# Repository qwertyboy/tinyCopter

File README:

tinyCopter v2 - arduino based quadcopter project

Specifications:
	-Atmega328 @ 16MHz
	-ADXL345 Accelerometer and ITG-3200 Gyroscope
	-USB for debugging and updating
	-Reads standard R/C receiver
	-Uses the AeroQuad firmware

----OLD VERSION----

tinyCopter rev C - xmega based quadcopter project

Specifications:
	-xmega32a4u @ 32MHz
	-ADXL345 Accelerometer and ITG-3200 Gyroscope
	-USB for debugging and updating
	-Reads standard R/C receiver

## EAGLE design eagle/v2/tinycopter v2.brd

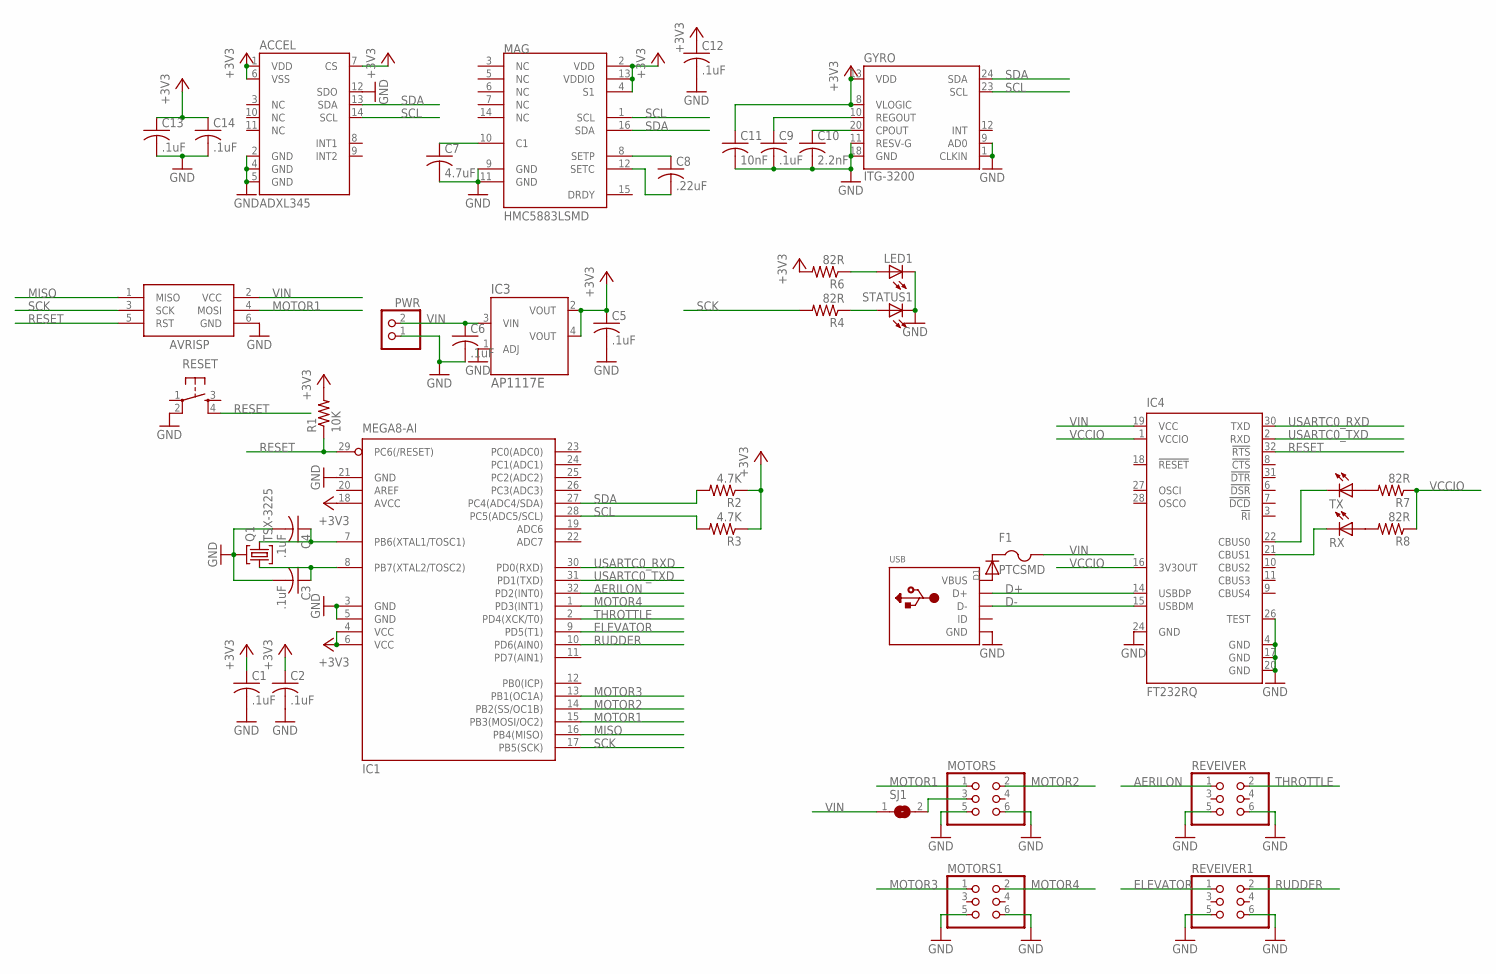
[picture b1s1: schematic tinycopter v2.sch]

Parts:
ACCEL: ADXL345; LGA14
AVRISP: AVRISP-6; AVRISP
C1, C2, C3, C4, C5, C6, C9, C12, C13, C14: .1uF; C0603
C7: 4.7uF; C0805K
C8: .22uF; C0603
C10: 2.2nF; C0603
C11: 10nF; C0603
D1: DIODESOD-123; SOD-123
F1: PTCSMD; 1812
GYRO: ITG-3200; QFN-24
IC1: MEGA8-AI; TQFP32-08
IC3: AP1117E; SOT223-3
IC4: FT232RQ; QFN32
LED1: LEDCHIP-LED0805; CHIP-LED0805
MAG: HMC5883LSMD; 16LPCC
MOTORS, MOTORS1: PINHD-2X3; 2X03
PWR: JST_2PIN-THM; JST-PH-2-THM
Q1: TSX-3225
R1: 10K; R0603
R2, R3: 4.7K; R0603
R4, R6, R7, R8: 82R; R0603
RESET: TAC_SWITCHSMD; TACTILE_SWITCH_SMD
REVEIVER, REVEIVER1: PINHD-2X3; 2X03
RX: LEDCHIP-LED0805; CHIP-LED0805
SJ1: SJ
STATUS1: LEDCHIP-LED0805; CHIP-LED0805
TX: LEDCHIP-LED0805; CHIP-LED0805
USB: USBMINIB; USB-MINIB

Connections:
+3V3: ACCEL.1 (VDD), ACCEL.6 (VSS), ACCEL.7 (CS), C1.1, C2.1, C5.1, C11.1, C12.1, C13.1, C14.1, GYRO.8 (VLOGIC), GYRO.13 (VDD), IC1.4 (VCC), IC1.6 (VCC), IC1.18 (AVCC), IC3.2 (VOUT), IC3.4 (VOUT), MAG.2 (VDD), MAG.4 (S1), MAG.13 (VDDIO), R1.2, R2.1, R3.1, R6.2
AERILON: IC1.32 (PD2(INT0)), REVEIVER.1
D+: IC4.14 (USBDP), USB.D+
D-: IC4.15 (USBDM), USB.D-
ELEVATOR: IC1.9 (PD5(T1)), REVEIVER1.1
GND: ACCEL.2 (GND), ACCEL.4 (GND), ACCEL.5 (GND), ACCEL.12 (SDO), AVRISP.6 (GND), C1.2, C2.2, C3.2, C4.2, C5.2, C6.2, C7.2, C9.2, C10.2, C11.2, C12.2, C13.2, C14.2, GYRO.1 (CLKIN), GYRO.9 (AD0), GYRO.11 (RESV-G), GYRO.18 (GND), IC1.3 (GND), IC1.5 (GND), IC1.21 (GND), IC3.1 (ADJ), IC4.4 (GND), IC4.17 (GND), IC4.20 (GND), IC4.24 (GND), IC4.26 (TEST), LED1.C, MAG.9 (GND), MAG.11 (GND), MOTORS.5, MOTORS.6, MOTORS1.5, MOTORS1.6, PWR.1 (2), Q1.2 (3), Q1.4 (3), RESET.2, REVEIVER.5, REVEIVER.6, REVEIVER1.5, REVEIVER1.6, STATUS1.C, USB.GND
MISO: AVRISP.1 (MISO), IC1.16 (PB4(MISO))
MOTOR1: AVRISP.4 (MOSI), IC1.15 (PB3(MOSI/OC2)), MOTORS.1
MOTOR2: IC1.14 (PB2(SS/OC1B)), MOTORS.2
MOTOR3: IC1.13 (PB1(OC1A)), MOTORS1.1
MOTOR4: IC1.1 (PD3(INT1)), MOTORS1.2
unnamed: C4.1, IC1.7 (PB6(XTAL1/TOSC1)), Q1.3 (2)
unnamed: C3.1, IC1.8 (PB7(XTAL2/TOSC2)), Q1.1
unnamed: R4.1, STATUS1.A
unnamed: C10.1, GYRO.20 (CPOUT)
unnamed: C7.1, MAG.10 (C1)
unnamed: C8.1, MAG.8 (SETP)
unnamed: LED1.A, R6.1
unnamed: C8.2, MAG.12 (SETC)
unnamed: C9.1, GYRO.10 (REGOUT)
unnamed: IC4.22 (CBUS0), TX.C
unnamed: IC4.21 (CBUS1), RX.C
unnamed: R7.2, TX.A
unnamed: D1.A, USB.VBUS
unnamed: R8.2, RX.A
unnamed: D1.C, F1.1
unnamed: MOTORS.3, SJ1.2
RESET: AVRISP.5 (RST), IC1.29 (PC6(/RESET)), IC4.32 (!RTS), R1.1, RESET.4
RUDDER: IC1.10 (PD6(AIN0)), REVEIVER1.2
SCK: AVRISP.3 (SCK), IC1.17 (PB5(SCK)), R4.2
SCL: ACCEL.14 (SCL), GYRO.23 (SCL), IC1.28 (PC5(ADC5/SCL)), MAG.1 (SCL), R3.2
SDA: ACCEL.13 (SDA), GYRO.24 (SDA), IC1.27 (PC4(ADC4/SDA)), MAG.16 (SDA), R2.2
THROTTLE: IC1.2 (PD4(XCK/T0)), REVEIVER.2
USARTC0_RXD: IC1.30 (PD0(RXD)), IC4.30 (TXD)
USARTC0_TXD: IC1.31 (PD1(TXD)), IC4.2 (RXD)
VCCIO: IC4.1 (VCCIO), IC4.16 (3V3OUT), R7.1, R8.1
VIN: AVRISP.2 (VCC), C6.1, F1.2, IC3.3 (VIN), IC4.19 (VCC), PWR.2 (1), SJ1.1

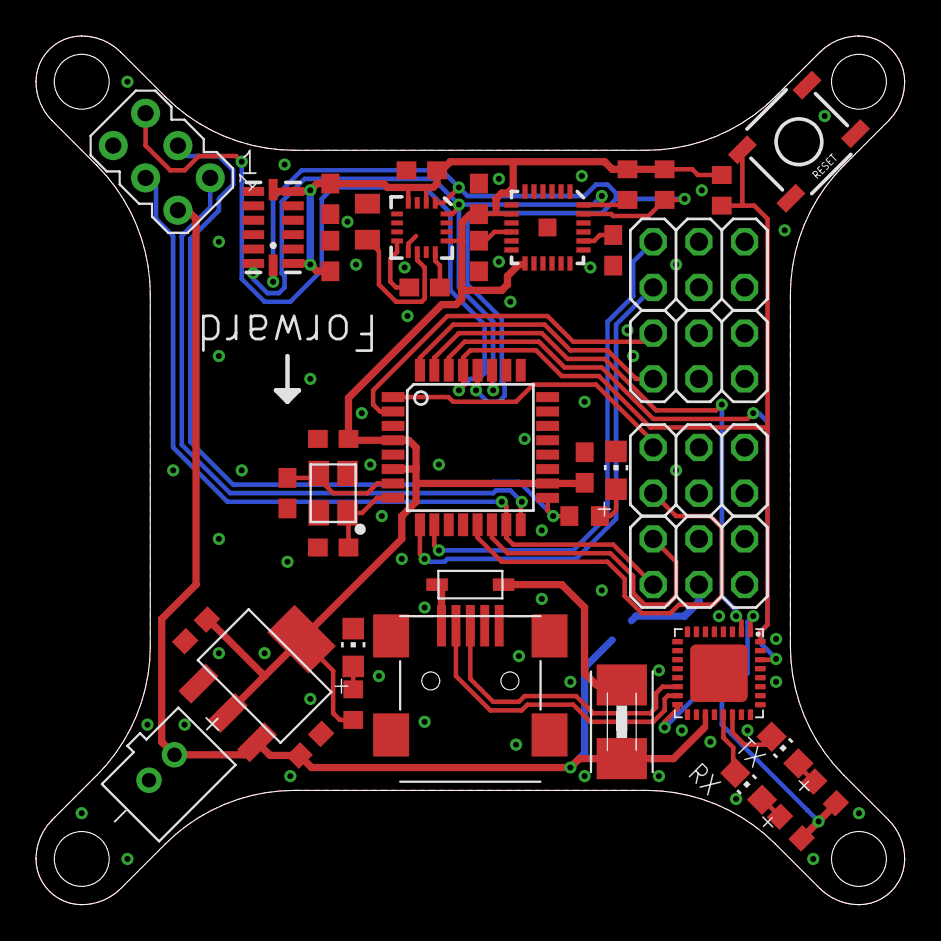
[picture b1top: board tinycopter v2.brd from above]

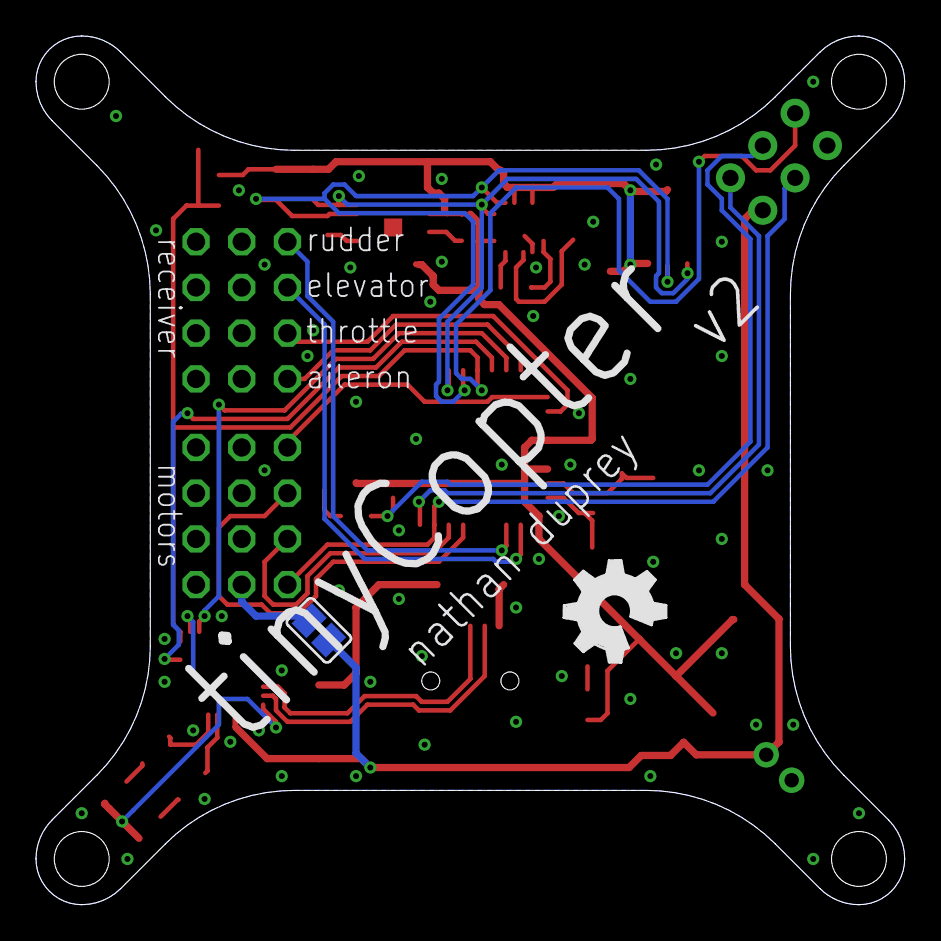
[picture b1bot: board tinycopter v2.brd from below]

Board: 2 copper layers, 48.3 x 48.3 mm, 44 parts (2 on the bottom side), 37 nets.

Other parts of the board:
U$1: OSHW_FILLX200_NOTEXT

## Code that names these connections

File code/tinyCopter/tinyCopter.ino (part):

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#define status_led1 13 //Pins for the status LEDs
#define status_led2 12

#define MOTOR1 0
#define MOTOR2 0
#define MOTOR3 0
#define MOTOR4 0

////////////////Target Angle Calculations////////////////

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  pinMode(status_led1, OUTPUT);  //Status LEDs are outputs
  pinMode(status_led2, OUTPUT);
  
  //pinMode(MOTOR1, OUTPUT);  //Motors are outputs
  //pinMode(MOTOR2, OUTPUT);
  //pinMode(MOTOR3, OUTPUT);
  //pinMode(MOTOR4, OUTPUT);
  
  Wire.begin();       //We are using TWIC on an xmega A4
  
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
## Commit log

2012-05-11 Added EAGLE schematic and layout files
2012-05-11 Moved EAGLE files for the mainboard
2012-05-11 Moving things around
2012-05-11 Added EAGLE schematic and layout files for tx/rx.
2012-06-22 Created the xmegrduino sketch
2012-08-02 Added revision C design and moved the rev B stuff
2012-08-02 Deleted folder
2012-08-05 Tweaked the board a bit
2012-09-15 Lots of progress on code. PWM works, working on input capture
2012-09-15 Cleaning up
2012-09-22 Most of the code is here. No idea if it works yet.
2012-09-22 Still getting there
2013-06-26 removed tx_rx folder, added eagle files for (hopefully) final version
